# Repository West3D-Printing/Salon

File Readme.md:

Files and documentation for the Salon board for Casa

# Why?
We wanted to provide a simple and inexpensive way to connect your Milo to the electronics bay of your Casa while allowing you to easily remove the Milo for service. The Salon PCB provides a "patchbay" to interconnect your MCU and the mill.

# How?
You can purchase the Salon board with wiring bundles at West3D here: https://west3d.com/products/milo-salon-de-la-casa-breakout-board-and-wiring-kit-for-milo-casa You're also welcome to produce your own PCB with our [KiCad files](kicad). The wiring is a simple 1:1 between the electronics bay and mill.

[STLs](stls) for a 3D printed PCB mount are in this repo. **There is now an updated version of the back mount with some improvements:**
1) More enclosed to keep chaff away from the connectors
2) An opening on the back to run wires upward for lighting (or whatever)
3) Slots at the bottom for zip ties to provide strain relief on the cables

The front hasn't changed and works with either back.

We've also included printable thumbscrews. These use a Voron standard brass heat insert and an M3x10 BHCS or SHCS, and make it easy to remove the Salon front without needing tools.

# Setup
Hardware you'll need for the mount:
| Fastener  | Quantity |
| ------------- | ------------- |
| M3x6 screw  | 2  |
| M3x8 screw  | 4  |
| M5x8 screw  | 4  |
| M3 heatset  | 6  |
| M5 roll-in nut  | 4  |

- Print the PCB mount.
- Insert two "Voron standard" M3 heat inserts in the back of the mount to hold the PCB, as well as two in the top and another two in the lower legs to hold the front of the case.
- The PCB is held in place with two M3x6 screws.

<sub>Please note this is the V1 mount back in the render</sub>
- After installing the PCB, attach the back of the mount to the rear upright in the Casa with four M5x8 screws and roll-in nuts.
- Connect the wiring from the electronics bay to the PCB, then connect the wiring from the mill. There's no defined in or out sides, all connections are are parallel.
- Once everything is patched install the front cover with four M3x8 screws to help keep chips away from the connections.

# What about all these other connections, like Aux?
We wanted to bring all the available ports of the Scylla board into the work area for whatever additional hardware you want to control. Caselights, air, coolant, disco balls…

# Why "Salon"?
The Casa is the "house" for the Milo- the central room in a casa is often called the salon.

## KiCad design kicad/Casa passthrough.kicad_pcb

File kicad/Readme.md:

Production files for the Salon PCB

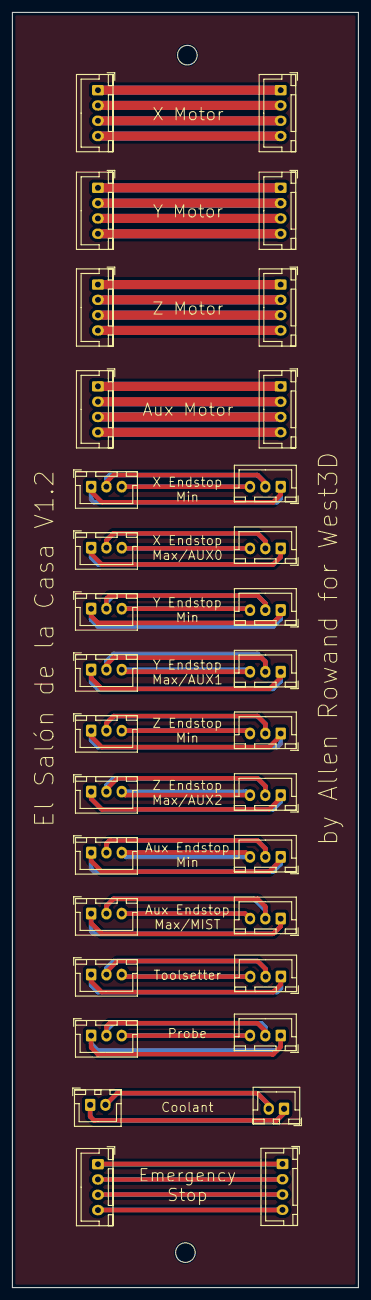
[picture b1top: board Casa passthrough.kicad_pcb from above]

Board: 2 copper layers, 56.5 x 208.3 mm, 32 parts (0 on the bottom side), 52 nets.

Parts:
Aux_Endstop_Max_IN1: Conn_01x03; JST_XH_B3B-XH-A_1x03_P2.50mm_Vertical
Aux_Endstop_Max_OUT1: Conn_01x03; JST_XH_B3B-XH-A_1x03_P2.50mm_Vertical
Aux_Endstop_Min_IN1: Conn_01x03; JST_XH_B3B-XH-A_1x03_P2.50mm_Vertical
Aux_Endstop_Min_OUT1: Conn_01x03; JST_XH_B3B-XH-A_1x03_P2.50mm_Vertical
Aux_Motor_IN1: Conn_01x04; JST_XH_B4B-XH-A_1x04_P2.50mm_Vertical
Aux_Motor_OUT1: Conn_01x04; JST_XH_B4B-XH-A_1x04_P2.50mm_Vertical
Coolant_IN1: Conn_01x03; JST_XH_B2B-XH-A_1x02_P2.50mm_Vertical
Coolant_OUT1: Conn_01x03; JST_XH_B2B-XH-A_1x02_P2.50mm_Vertical
EStop_OUT1: Conn_01x04; JST_XH_B4B-XH-A_1x04_P2.50mm_Vertical
Estop_IN1: Conn_01x04; JST_XH_B4B-XH-A_1x04_P2.50mm_Vertical
Probe_IN1: Conn_01x03; JST_XH_B3B-XH-A_1x03_P2.50mm_Vertical
Probe_OUT1: Conn_01x03; JST_XH_B3B-XH-A_1x03_P2.50mm_Vertical
Toolsetter_IN1: Conn_01x03; JST_XH_B3B-XH-A_1x03_P2.50mm_Vertical
Toolsetter_OUT1: Conn_01x03; JST_XH_B3B-XH-A_1x03_P2.50mm_Vertical
X_Endstop_Max_IN1: Conn_01x03; JST_XH_B3B-XH-A_1x03_P2.50mm_Vertical
X_Endstop_Max_OUT1: Conn_01x03; JST_XH_B3B-XH-A_1x03_P2.50mm_Vertical
X_Endstop_Min_IN1: Conn_01x03; JST_XH_B3B-XH-A_1x03_P2.50mm_Vertical
X_Endstop_Min_OUT1: Conn_01x03; JST_XH_B3B-XH-A_1x03_P2.50mm_Vertical
X_Motor_IN1: Conn_01x04; JST_XH_B4B-XH-A_1x04_P2.50mm_Vertical
X_Motor_OUT1: Conn_01x04; JST_XH_B4B-XH-A_1x04_P2.50mm_Vertical
Y_Endstop_Max_IN1: Conn_01x03; JST_XH_B3B-XH-A_1x03_P2.50mm_Vertical
Y_Endstop_Max_OUT1: Conn_01x03; JST_XH_B3B-XH-A_1x03_P2.50mm_Vertical
Y_Endstop_Min_IN1: Conn_01x03; JST_XH_B3B-XH-A_1x03_P2.50mm_Vertical
Y_Endstop_Min_OUT1: Conn_01x03; JST_XH_B3B-XH-A_1x03_P2.50mm_Vertical
Y_Motor_IN1: Conn_01x04; JST_XH_B4B-XH-A_1x04_P2.50mm_Vertical
Y_Motor_OUT1: Conn_01x04; JST_XH_B4B-XH-A_1x04_P2.50mm_Vertical
Z_Endstop_Max_IN1: Conn_01x03; JST_XH_B3B-XH-A_1x03_P2.50mm_Vertical
Z_Endstop_Max_OUT1: Conn_01x03; JST_XH_B3B-XH-A_1x03_P2.50mm_Vertical
Z_Endstop_Min_IN1: Conn_01x03; JST_XH_B3B-XH-A_1x03_P2.50mm_Vertical
Z_Endstop_Min_OUT1: Conn_01x03; JST_XH_B3B-XH-A_1x03_P2.50mm_Vertical
Z_Motor_IN1: Conn_01x04; JST_XH_B4B-XH-A_1x04_P2.50mm_Vertical
Z_Motor_OUT1: Conn_01x04; JST_XH_B4B-XH-A_1x04_P2.50mm_Vertical

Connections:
unnamed: Aux_Endstop_Max_IN1.1, Aux_Endstop_Max_OUT1.1
unnamed: Aux_Endstop_Max_IN1.2, Aux_Endstop_Max_OUT1.2
unnamed: Aux_Endstop_Max_IN1.3, Aux_Endstop_Max_OUT1.3
unnamed: Aux_Endstop_Min_IN1.1, Aux_Endstop_Min_OUT1.1
unnamed: Aux_Endstop_Min_IN1.2, Aux_Endstop_Min_OUT1.2
unnamed: Aux_Endstop_Min_IN1.3, Aux_Endstop_Min_OUT1.3
unnamed: Aux_Motor_IN1.1, Aux_Motor_OUT1.1
unnamed: Aux_Motor_IN1.2, Aux_Motor_OUT1.2
unnamed: Aux_Motor_IN1.3, Aux_Motor_OUT1.3
unnamed: Aux_Motor_IN1.4, Aux_Motor_OUT1.4
unnamed: Coolant_IN1.1, Coolant_OUT1.1
unnamed: Coolant_IN1.2, Coolant_OUT1.2
unnamed: EStop_OUT1.1, Estop_IN1.1
unnamed: EStop_OUT1.2, Estop_IN1.2
unnamed: EStop_OUT1.3, Estop_IN1.3
unnamed: EStop_OUT1.4, Estop_IN1.4
unnamed: Probe_IN1.1, Probe_OUT1.1
unnamed: Probe_IN1.2, Probe_OUT1.2
unnamed: Probe_IN1.3, Probe_OUT1.3
unnamed: Toolsetter_IN1.1, Toolsetter_OUT1.1
unnamed: Toolsetter_IN1.2, Toolsetter_OUT1.2
unnamed: Toolsetter_IN1.3, Toolsetter_OUT1.3
unnamed: X_Endstop_Max_IN1.1, X_Endstop_Max_OUT1.1
unnamed: X_Endstop_Max_IN1.2, X_Endstop_Max_OUT1.2
unnamed: X_Endstop_Max_IN1.3, X_Endstop_Max_OUT1.3
unnamed: X_Endstop_Min_IN1.1, X_Endstop_Min_OUT1.1
unnamed: X_Endstop_Min_IN1.2, X_Endstop_Min_OUT1.2
unnamed: X_Endstop_Min_IN1.3, X_Endstop_Min_OUT1.3
unnamed: X_Motor_IN1.1, X_Motor_OUT1.1
unnamed: X_Motor_IN1.2, X_Motor_OUT1.2
unnamed: X_Motor_IN1.3, X_Motor_OUT1.3
unnamed: X_Motor_IN1.4, X_Motor_OUT1.4
unnamed: Y_Endstop_Max_IN1.1, Y_Endstop_Max_OUT1.1
unnamed: Y_Endstop_Max_IN1.2, Y_Endstop_Max_OUT1.2
unnamed: Y_Endstop_Max_IN1.3, Y_Endstop_Max_OUT1.3
unnamed: Y_Endstop_Min_IN1.1, Y_Endstop_Min_OUT1.1
unnamed: Y_Endstop_Min_IN1.2, Y_Endstop_Min_OUT1.2
unnamed: Y_Endstop_Min_IN1.3, Y_Endstop_Min_OUT1.3
unnamed: Y_Motor_IN1.1, Y_Motor_OUT1.1
unnamed: Y_Motor_IN1.2, Y_Motor_OUT1.2
unnamed: Y_Motor_IN1.3, Y_Motor_OUT1.3
unnamed: Y_Motor_IN1.4, Y_Motor_OUT1.4
unnamed: Z_Endstop_Max_IN1.1, Z_Endstop_Max_OUT1.1
unnamed: Z_Endstop_Max_IN1.2, Z_Endstop_Max_OUT1.2
unnamed: Z_Endstop_Max_IN1.3, Z_Endstop_Max_OUT1.3
unnamed: Z_Endstop_Min_IN1.1, Z_Endstop_Min_OUT1.1
unnamed: Z_Endstop_Min_IN1.2, Z_Endstop_Min_OUT1.2
unnamed: Z_Endstop_Min_IN1.3, Z_Endstop_Min_OUT1.3
unnamed: Z_Motor_IN1.1, Z_Motor_OUT1.1
unnamed: Z_Motor_IN1.2, Z_Motor_OUT1.2
unnamed: Z_Motor_IN1.3, Z_Motor_OUT1.3
unnamed: Z_Motor_IN1.4, Z_Motor_OUT1.4

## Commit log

2025-04-17 Initial upload
2025-04-21 Upload case STLs
2025-09-24 Add V2 and thumbscrew STLs
2025-09-24 Update images
2025-09-24 Correct image extensions
2025-09-24 Upload step files
